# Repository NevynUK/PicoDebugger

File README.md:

# PicoDebugger

The PicoDebugger project is an extension the Raspberry Pi Foundations PicoProbe project.  The basis of the PicoProbe is to use a Raspberry Pi Pico to act as a debug probe for another Pico.

There are two elements to this project:

* PicoProbe Software (from Raspberry Pi Foundation)
* PicoDebugger hardware

The aim is to provide a physically stable set up for the debug probe, the target Pico and to also allow connection to hardware under development.

This document will use the following terminology:

* Picoprobe - the Raspberry Pi Pico programmed with the PicoProbe software.  This will act as a debug probe for the host computer.
* Target - this is the Raspberry Pi Pico that is being debugged.

## History

The idea came about as I was developing some software using the NuttX RTOS on the Pico.  I had some spare Pico boards available, it was just a case of wiring them up.  The Fritzing diagram in the Raspberry [Getting Started Guide](https://datasheets.raspberrypi.com/pico/getting-started-with-pico.pdf) shows how to connect a Pico as a debug probe to a target Pico:

This lead to a quick hack and a development board put together on protoboard:

The next step is to break out KiCad an put together a solution that will allow connections from the target board to additional development hardware.

## PicoProbe Software

The Raspberry Pi Foundation have done the hard work by producing the software for the PicoProbe and the PicoDebug probe.  You can find more information in the [PicoProbe GitHub Repository](https://github.com/raspberrypi/picoprobe).  This repository contains the links to the documents detailing how to set up a Pico as a debug probe.

The software allows for two types of connection:

* SWD debug
* UART

SWD allows the host computer to connect to the target board and deploy and debug applications running on the board.

The UART connection will allow the application to generate user messages and also accept input from the host computer.

## PicoDebugger Hardware

The PicoDebugger aims to provide the following features:

* Mount a Pico to act as a Picoprobe
* Mount a target Pico
* Optionally connect UART from the target to the Picoprobe
* Reset the target board to allow programming by dragging a UF2 file to the target board
* Deployment and debugging using SWD
* Connection to external project hardware

Thanks to KiCad and [PCBWay](https://www.pcbway.com/), a few weeks later we have this:

Moving from the left to the right of the board.  The left of the board shows the Picoprobe soldered to the board.

The DIP switches allow the two UART lines between the Picoprobe and the target board to be connected / disconnected as required.

The three pin header to be connected to the SWD pins on the Pico or Pico W board.

The reset switch is connected to the reset pin on the target board allowing the target board to be programmed by dragging a UF2 file onto the board.

To the far right there is a 2x20 pin header which matches the pins on the target board.  Tis will allow the target board to be connected to development hardware.  This could be using individual dupont cables for a small number of connections or using an IDE cable to connect all 40 pins through to a project under development.

The full designs (KiCad 7) of this board are available in the [PCB](PCB) directory.

## PicoDebugger Mount

The image above shows the PicoDebugger board on a 3D printed base.  This base keeps the through hole parts from scratching and work surfaces and helps to reduce the possibility of unintended shorts on the exposed pins on the bottom of the board.

This part is available as a Fusion 360 part in the [3DDesigns](3DDesigns) folder.  This folder also contains the GCode the design.  The GCode is intended to be used on an Ender 3 Pro, using PLA.  The print has a 50% infill for rigidity.

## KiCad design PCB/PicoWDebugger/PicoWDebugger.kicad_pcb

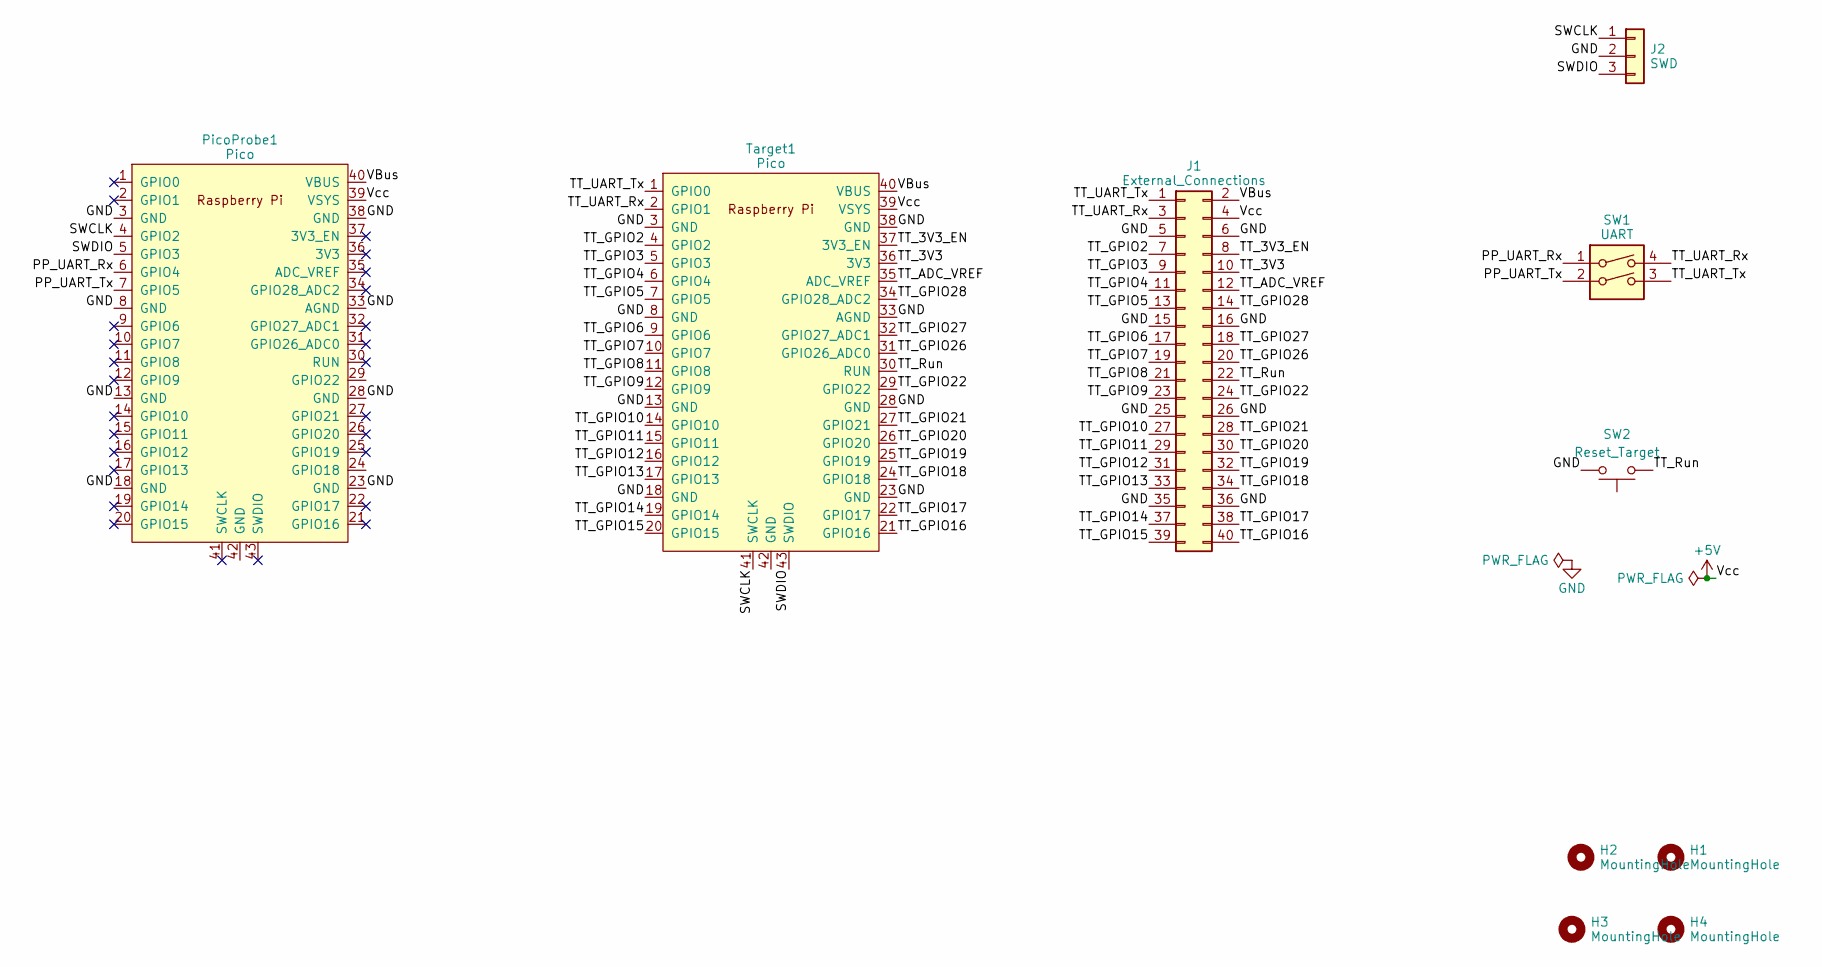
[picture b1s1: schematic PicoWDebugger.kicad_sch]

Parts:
H1, H2, H3, H4: MountingHole; MountingHole_2.5mm
J1: External_Connections; PinHeader_2x20_P2.54mm_Vertical
J2: SWD; PinHeader_1x03_P2.54mm_Vertical
PicoProbe1: Pico; RPi_Pico_SMD_TH
SW1: UART; SW_DIP_SPSTx02_Slide_9.78x7.26mm_W7.62mm_P2.54mm
SW2: Reset_Target; Alps_SKRGAFD010
Target1: Pico; RPi_Pico_W_SMD_TH

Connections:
+5V: J1.4, PicoProbe1.39 (VSYS), Target1.39 (VSYS)
/PP_UART_Rx: PicoProbe1.6 (GPIO4), SW1.1
/PP_UART_Tx: PicoProbe1.7 (GPIO5), SW1.2
/SWCLK: J2.1, PicoProbe1.4 (GPIO2), Target1.41 (SWCLK)
/SWDIO: J2.3, PicoProbe1.5 (GPIO3), Target1.43 (SWDIO)
/TT_3V3: J1.10, Target1.36 (3V3)
/TT_3V3_EN: J1.8, Target1.37 (3V3_EN)
/TT_ADC_VREF: J1.12, Target1.35 (ADC_VREF)
/TT_GPIO2: J1.7, Target1.4 (GPIO2)
/TT_GPIO3: J1.9, Target1.5 (GPIO3)
/TT_GPIO4: J1.11, Target1.6 (GPIO4)
/TT_GPIO5: J1.13, Target1.7 (GPIO5)
/TT_GPIO6: J1.17, Target1.9 (GPIO6)
/TT_GPIO7: J1.19, Target1.10 (GPIO7)
/TT_GPIO8: J1.21, Target1.11 (GPIO8)
/TT_GPIO9: J1.23, Target1.12 (GPIO9)
/TT_GPIO10: J1.27, Target1.14 (GPIO10)
/TT_GPIO11: J1.29, Target1.15 (GPIO11)
/TT_GPIO12: J1.31, Target1.16 (GPIO12)
/TT_GPIO13: J1.33, Target1.17 (GPIO13)
/TT_GPIO14: J1.37, Target1.19 (GPIO14)
/TT_GPIO15: J1.39, Target1.20 (GPIO15)
/TT_GPIO16: J1.40, Target1.21 (GPIO16)
/TT_GPIO17: J1.38, Target1.22 (GPIO17)
/TT_GPIO18: J1.34, Target1.24 (GPIO18)
/TT_GPIO19: J1.32, Target1.25 (GPIO19)
/TT_GPIO20: J1.30, Target1.26 (GPIO20)
/TT_GPIO21: J1.28, Target1.27 (GPIO21)
/TT_GPIO22: J1.24, Target1.29 (GPIO22)
/TT_GPIO26: J1.20, Target1.31 (GPIO26_ADC0)
/TT_GPIO27: J1.18, Target1.32 (GPIO27_ADC1)
/TT_GPIO28: J1.14, Target1.34 (GPIO28_ADC2)
/TT_Run: J1.22, SW2.1, Target1.30 (RUN)
/TT_UART_Rx: J1.3, SW1.4, Target1.2 (GPIO1)
/TT_UART_Tx: J1.1, SW1.3, Target1.1 (GPIO0)
/VBus: J1.2, PicoProbe1.40 (VBUS), Target1.40 (VBUS)
GND: J1.5, J1.6, J1.15, J1.16, J1.25, J1.26, J1.35, J1.36, J2.2, PicoProbe1.3 (GND), PicoProbe1.8 (GND), PicoProbe1.13 (GND), PicoProbe1.18 (GND), PicoProbe1.23 (GND), PicoProbe1.28 (GND), PicoProbe1.33 (AGND), PicoProbe1.38 (GND), SW2.2, Target1.3 (GND), Target1.8 (GND), Target1.13 (GND), Target1.18 (GND), Target1.23 (GND), Target1.28 (GND), Target1.33 (AGND), Target1.38 (GND)

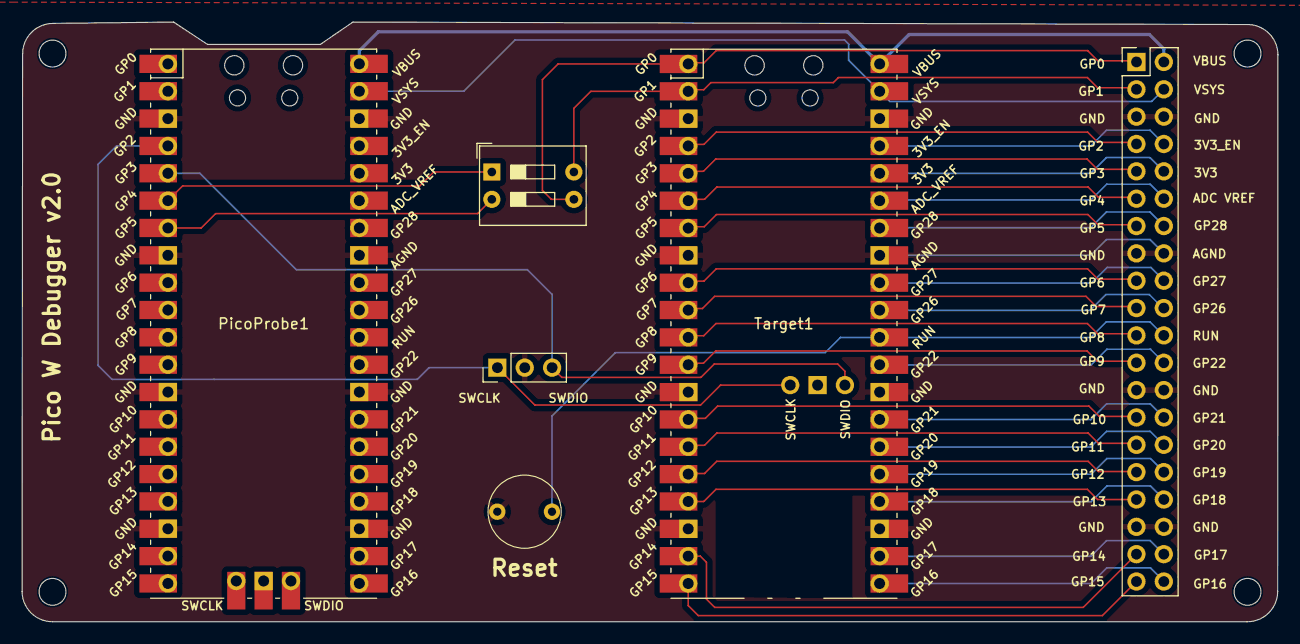
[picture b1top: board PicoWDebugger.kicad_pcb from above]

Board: 2 copper layers, 116.7 x 55.7 mm, 10 parts (0 on the bottom side), 37 nets.

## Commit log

2023-07-05 Add some documentation
2023-07-05 VSCode spelling settings
2023-07-05 Add frame 3D Model
2023-07-05 Add PCB design.
2023-07-15 Connected VBus and added text
2023-07-15 Ignore DS_Store
2023-11-23 Version 2 changes.
2023-11-25 Updated design, added PicoW version
